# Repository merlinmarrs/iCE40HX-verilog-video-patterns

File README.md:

# Video FPGA Dev Board

A Lattice iCE40HX1K-based FPGA developement board for live-playable video experiments.

|                          |                          |
:-------------------------:|:-------------------------:
  | 

# Features :

- 9-key mechanical button interface
- Relatively low-cost, single board design
- HDMI and VGA out
- Reverse polarity and fuse protection

# Minimal BOM :

[Excel BOM Mouser / Digikey ](https://github.com/merlinmarrs/iCE40HX-verilog-video-patterns/tree/main/PCB%20files)

- 9x Mechanical keyboard keys
- 1x FPGA iCE40HX1K-TQ144
- 1x 100MHz clock oscillator
- 1x SRAM 2Mb 256Kx8
- 1x Flash N25Q032A13ESC40F
- 1x USB-C SMD 6 pin connector
- 1x 3.3V reg TLV73333PDBVT 
- 1x 1.2V reg TLV73312PDBVT
- 1x PFET
- 1x Resettable Fuse
- 1x D-SUB 15 connector
- 1x HDMI Connector 
- 50x 0.1µF capacitor 0805
- 50x  10kΩ, 1.8kΩ, 1kΩ, 470Ω, 270Ω, 120Ω resistors 0805
- 5x LEDs 0805
- 2x Dual-row headers

optional extras : (1x Raspberry Pi Zero, 1x Micro SD holder, 2x 10kΩ potentiometers, 1x fast op-amp, 1x 3.5mm audio jack, 1x dual SMD dip switch, 1x SMD pushbutton)

# PCB files

[KiCAD and Eagle PCBs](https://github.com/merlinmarrs/iCE40HX-verilog-video-patterns/tree/main/PCB%20files)

# HDL files

[Verilog, Pin constraints, and synthesized binaries ](https://github.com/merlinmarrs/iCE40HX-verilog-video-patterns/tree/main/verilog)

To compile and upload files :

[Yoysis Open-source Toolchain ](https://github.com/YosysHQ/yosys)

[iCEcube2 Toolchain](https://www.latticesemi.com/iCEcube2)

## Acknowledgements

Mike Field <hamster@snap.net.nz> for his minimalDVID_encoder.vhd : A quick and dirty DVI-D implementation

OLIMEX FPGA dev board https://github.com/OLIMEX/iCE40HX1K-EVB/tree/master

ALHAMBRA FPGA https://github.com/FPGAwars/Alhambra-II-FPGA/tree/master

HDL Bits https://hdlbits.01xz.net/wiki/Main_Page

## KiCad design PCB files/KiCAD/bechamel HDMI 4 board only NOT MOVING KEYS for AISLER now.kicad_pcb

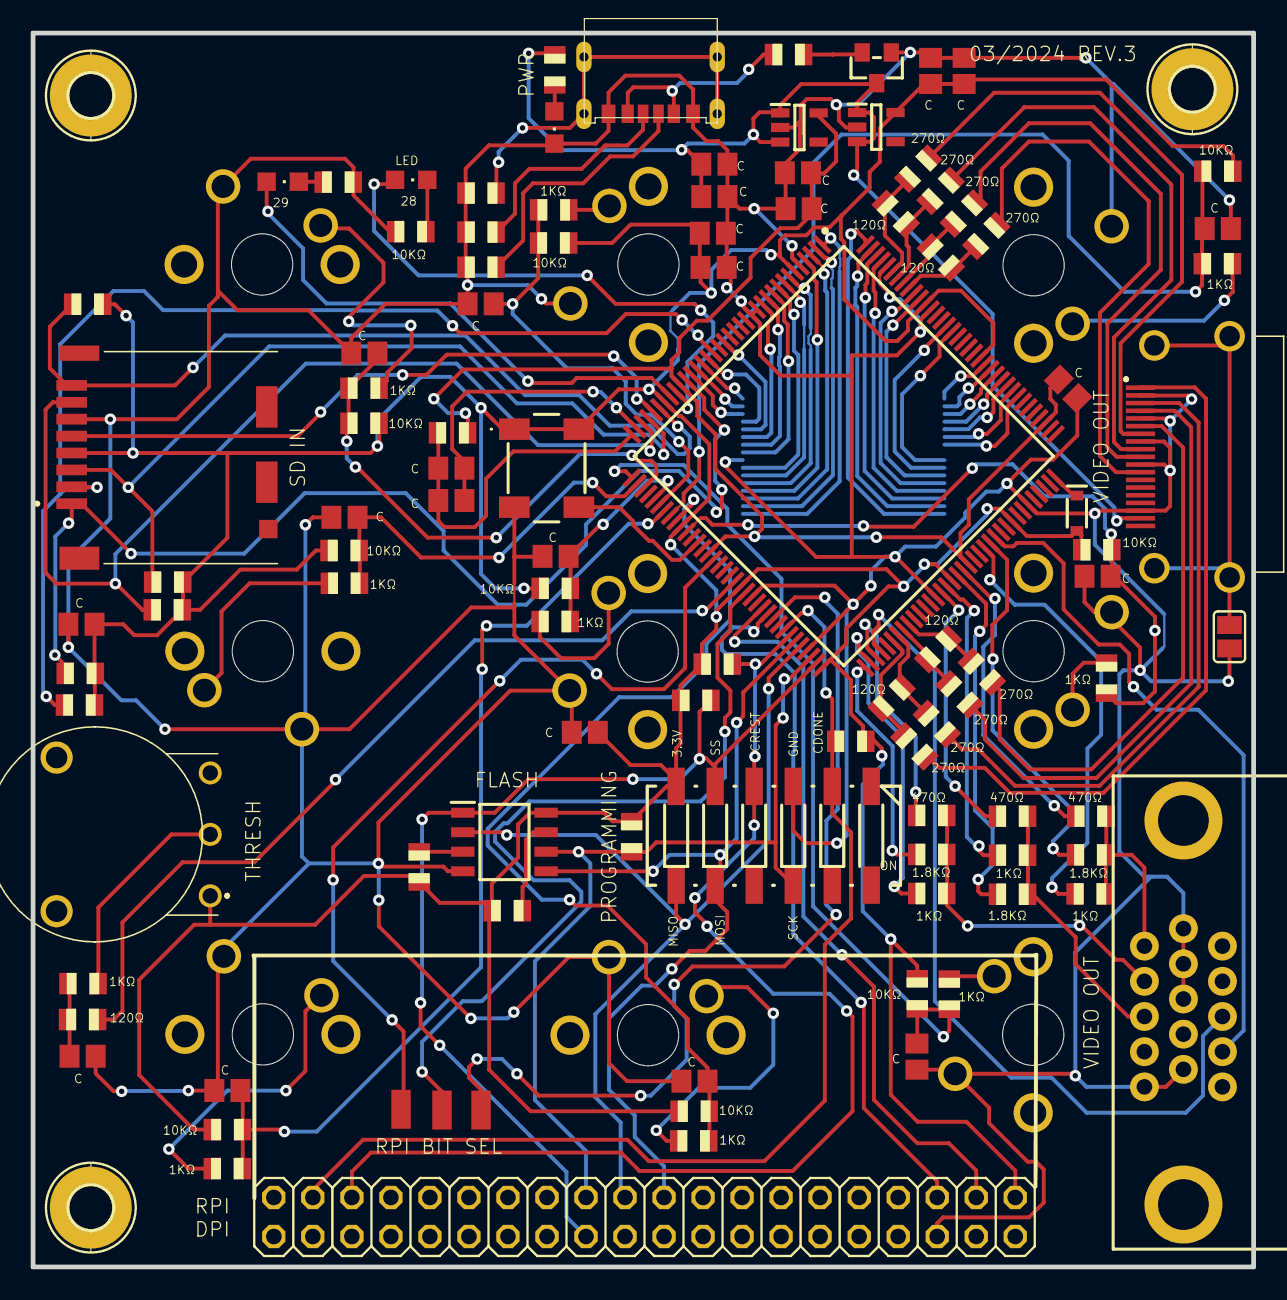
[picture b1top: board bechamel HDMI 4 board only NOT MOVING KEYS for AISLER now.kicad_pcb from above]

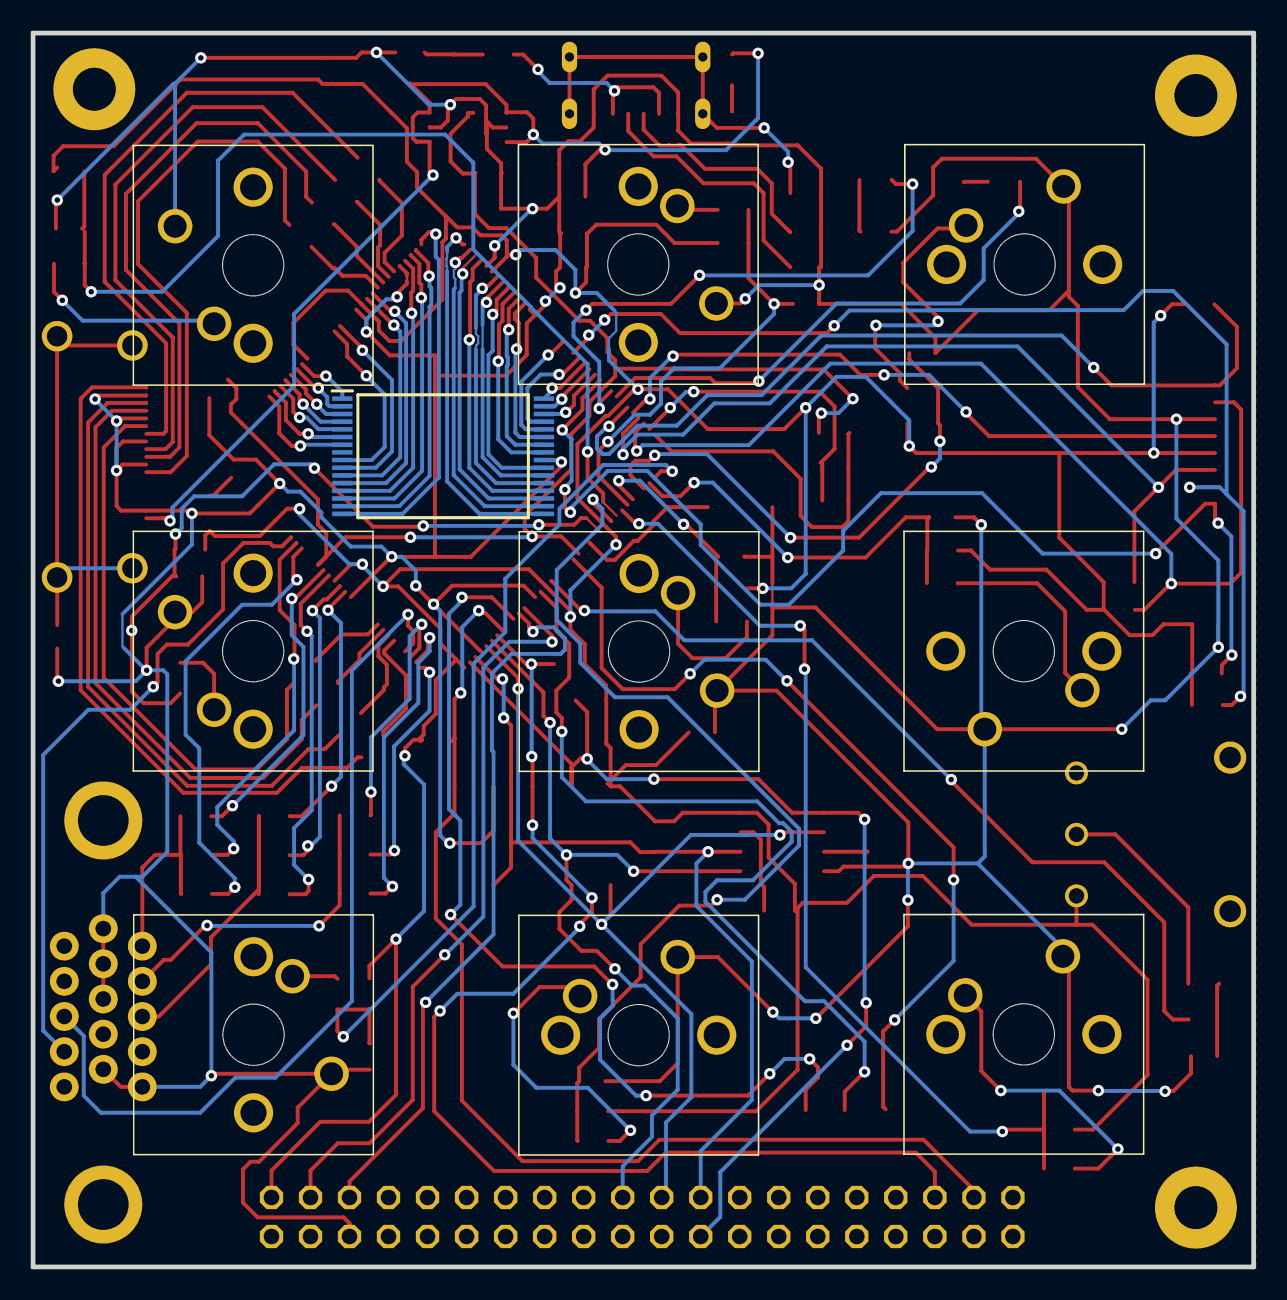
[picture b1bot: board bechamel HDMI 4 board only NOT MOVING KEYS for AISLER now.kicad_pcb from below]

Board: 2 copper layers, 79.5 x 80.3 mm, 117 parts (10 on the bottom side), 119 nets.

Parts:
C1, C6, C7, C8, C9, C10, C11, C12, C13, C14, C15, C18, C21, C22, C25, C26, C27: 0.1uF; C0805
C3, C4, C5, C16, C23: 10uF; C0805
C17: 5.6nF; C0805
D1: 250mA/100V; SOD-323
FUSE0: FUSE; R0805
H1, H5, H6: MOUNT-PAD-ROUND2.8; 2,8-PAD
IC1: TLV73333PDBVT; SOT95P280X145-5N
IC2: ICE40HX1K-TQ144; QFP50P2200X2200X160-144N
IC3: TLV73312PDBVT; SOT95P280X145-5N
IC4: N25Q032A13ESC40F; SOIC127P600X175-8N
IC6: IS62WV2568BLL-55HLI; SOP50P1340X125-32N
J2: SS-53000-001; SS53000001
J3: DM3CS-SF; DM3CSSF
JP1: 2X20
LED6, LED12, LED13: CHIPLED_0805
P-FET2: SOT23-WIDE
PAD1, PAD2, PAD3: SMD1,27-2,54
R1, R17, R25: 470R; R0805
R2, R5, R7, R15, R18, R22, R24, R26, R47, R49, R51, R53: 1K; R0805
R3, R4, R6, R8, R9, R10, R11, R12, R13, R21, R23, R45, R46, R48, R50, R52, R54, R55, R58, R59: 10K; R0805
R14, R36, R37: 100 ohm; R0805
R16, R20, R27: 1.8K; R0805
R19: 300 ohm; R0805
R28, R29, R31, R32, R34, R35, R39, R40: 270R; R0805
R30, R33, R38, R41: 120R; R0805
R42: 1M; R0805
R43, R44: 5k1; R0805
R56: 1K8 ohm; R0805
R57: 180 ohm; R0805
S1, S2, S3, S4, S5, S6, S7, S8, S13: MX1A-11NW; MX1A11NW
S9: 219-06J; CTS-219-06J
SJ2: SJ
U$1: DB15
U$2: USBC-6P; USCX-06FX-XXMX-01
VR1: RV100F-30-4K1B-B10K-B301; RV100F304K1BB10KB301
Y2: ECS-3953M-080-BN-T-TR; ECS3953M080BNTTR

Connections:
1.2V: C4.1, C26.1, C27.1, IC2.27, IC2.51, IC2.92, IC2.111, IC3.5, R14.2
3.3V: C12.1, C15.1, C16.2, C18.1, C21.1, C25.1, D1.A, IC1.5, IC2.6, IC2.30, IC2.46, IC2.57, IC2.72, IC2.89, IC2.100, IC2.123, IC2.133, IC4.8, J3.4, JP1.1, R3.2, R4.2, R6.2, R8.2, R9.2, R10.2, R11.2, R12.2, R13.2, R21.2, R23.2, R45.2, R46.2, R48.2, R50.2, R52.2, R54.2, R55.1, R58.2, R59.2, S9.6, VR1.1, Y2.1, Y2.4
5V: C3.1, C5.1, IC1.1, IC1.3, IC3.1, IC3.3, J2.18, P-FET2.3, R19.2
5V?: FUSE0.1, P-FET2.2
A0: IC2.4, IC6.20
A1: IC2.3, IC6.19
A2: IC2.2, IC6.18
A3: IC2.1, IC6.17
A4: IC2.144, IC6.16
A5: IC2.143, IC6.15
A6: IC2.142, IC6.14
A7: IC2.141, IC6.13
A8: IC2.120, IC6.3
A9: IC2.121, IC6.2
A10: IC2.24, IC6.31
A11: IC2.122, IC6.1
A12: IC2.135, IC6.12
A13: IC2.119, IC6.4
A14: IC2.134, IC6.11
A15: IC2.116, IC6.7
A16: IC2.129, IC6.10
A17: IC2.128, IC6.9
ADC_IN: IC2.56, R57.2
BLUE: R1.2, R15.2, R16.2, U$1.3
BLUE_1: IC2.87, R1.1
BLUE_2: IC2.88, R15.1
BLUE_3: IC2.90, R16.1
CLK+: IC2.137, R39.2, R41.1
CLK-: IC2.136, R40.2, R41.2
CMD: IC2.33, J3.3, R54.1
CS2: IC2.117, IC6.6
DAT0: IC2.34, J3.7, R55.2
DAT1: IC2.31, J3.8, R59.1
DAT2: IC2.26, J3.1, R45.1
DAT3: IC2.21, J3.2, R58.1
DATA0+: IC2.139, R34.2, R38.1
DATA0-: IC2.138, R35.2, R38.2
DATA1+: IC2.80, R31.2, R33.1
DATA1-: IC2.81, R32.2, R33.2
DATA2+: IC2.78, R28.2, R30.1
DATA2-: IC2.79, R29.2, R30.2
FPGA_CLK: IC2.49, Y2.3
GND: C1.1, C3.2, C4.2, C5.2, C6.1, C7.1, C8.1, C9.1, C10.1, C11.1, C12.2, C13.1, C14.1, C15.2, C16.1, C17.1, C18.2, C21.2, C25.2, C26.2, C27.2, IC1.2, IC2.5, IC2.13, IC2.14, IC2.59, IC2.69, IC2.86, IC2.103, IC2.132, IC2.140, IC3.2, IC4.4, IC6.24, J2.2, J2.5, J2.8, J2.11, J2.17, J3.6, JP1.6, LED6.C, P-FET2.1, R36.1, R37.1, R42.2, R43.2, R44.2, S1.2, S2.2, S3.2, S4.2, S5.2, S6.2, S7.2, S8.2, S9.3, S13.2, SJ2.2, U$1.5, U$1.6, U$1.7, U$1.8, U$1.10, U$2.GND1, U$2.GND2, Y2.2
GREEN: R17.2, R18.2, R20.2, U$1.2
GREEN_1: IC2.75, R17.1
GREEN_2: IC2.74, R18.1
GREEN_3: IC2.73, R20.1
H_SYNC: IC2.76, U$1.13
H_SYNC_IN: IC2.62, JP1.5
I/O0: IC2.7, IC6.21
I/O1: IC2.8, IC6.22
I/O2: IC2.9, IC6.23
I/O3: IC2.10, IC6.25
I/O4: IC2.11, IC6.26
I/O5: IC2.12, IC6.27
I/O6: IC2.19, IC6.28
I/O7: IC2.22, IC6.29
ICE_CDONE: IC2.65, JP1.37, R8.1, S9.2
ICE_CREST: IC2.66, JP1.35, R9.1, S9.4
ICE_MISO: IC2.68, IC4.2, JP1.21, S9.7
ICE_MOSI: IC2.67, IC4.5, JP1.19, S9.8
ICE_SCK: IC2.70, IC4.6, JP1.23, R13.1, S9.10
ICE_SS_B: IC2.71, IC4.1, JP1.24, R12.1, S9.5
KEY_0: C13.2, IC2.37, R50.1, R51.2
KEY_0_LED: IC2.28, LED12.A
KEY_1: C6.2, IC2.38, R3.1, R5.2
KEY_1_LED: IC2.29, LED13.A
KEY_2: C11.2, IC2.39, R48.1, R49.2
KEY_3: C1.2, IC2.41, R2.2, R4.1
KEY_4: C10.2, IC2.42, R46.1, R47.2
KEY_5: C7.2, IC2.43, R6.1, R7.2
KEY_6: C9.2, IC2.44, R23.1, R24.2
KEY_7: C8.2, IC2.45, R21.1, R22.2
KEY_8: C14.2, IC2.47, R52.1, R53.2
unnamed: IC4.7, R10.1
unnamed: LED6.A, R19.1
unnamed: IC4.3, R11.1
unnamed: R43.1, U$2.CC2
unnamed: D1.C, IC2.108
unnamed: C22.2, C23.2, IC2.35
unnamed: C22.1, C23.1, IC2.36, R14.1
unnamed: R42.1, U$2.SHIELD1, U$2.SHIELD2, U$2.SHIELD3, U$2.SHIELD4
unnamed: R56.2, VR1.2
unnamed: J2.1, R28.1
unnamed: R44.1, U$2.CC1
unnamed: J2.MH1, J2.MH2, J2.MH3, J2.MH4, SJ2.1
unnamed: C17.2, R56.1, R57.1
unnamed: J2.3, R29.1
unnamed: J2.4, R31.1
unnamed: LED12.C, R36.2
unnamed: LED13.C, R37.2
unnamed: J2.6, R32.1
unnamed: IC2.52, PAD1.1
unnamed: J2.7, R34.1
unnamed: J2.9, R35.1
unnamed: J2.10, R39.1
unnamed: J2.12, R40.1
unnamed: R2.1, S6.1
unnamed: R5.1, S5.1
unnamed: R7.1, S7.1
unnamed: R22.1, S8.1
unnamed: R24.1, S3.1
unnamed: R47.1, S2.1
unnamed: R49.1, S1.1
unnamed: R51.1, S13.1
unnamed: R53.1, S4.1
unnamed: IC2.58, PAD2.1
unnamed: IC2.63, PAD3.1
PRE_FUSE: FUSE0.2, U$2.VBUS1, U$2.VBUS2
RED: R25.2, R26.2, R27.2, U$1.1
RED_1: IC2.91, R25.1
RED_2: IC2.95, R26.1
RED_3: IC2.96, R27.1
SD_CLK: IC2.32, J3.5
V_SYNC: IC2.97, U$1.14
V_SYNC_IN: IC2.61, JP1.3
~CS1: IC2.25, IC6.30
~OE: IC2.23, IC6.32
~WE: IC2.118, IC6.5

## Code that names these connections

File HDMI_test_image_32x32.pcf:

set_io hdmi_p[0] 139 -io_std SB_LVCMOS
set_io hdmi_p[2] 78 -io_std SB_LVCMOS
set_io hdmi_p[1] 80 -io_std SB_LVCMOS
set_io hdmi_p[3] 137 -io_std SB_LVCMOS

set_io hdmi_n[0] 138 -io_std SB_LVCMOS
set_io hdmi_n[2] 79 -io_std SB_LVCMOS
set_io hdmi_n[1] 81 -io_std SB_LVCMOS
set_io hdmi_n[3] 136 -io_std SB_LVCMOS

set_io key[0] 37
set_io key[1] 38
set_io key[2] 39
set_io key[3] 41
set_io key[4] 42
set_io key[5] 43
set_io key[6] 44
set_io key[7] 45
set_io rec 47

set_io SCK 32
set_io CMD 33

set_io LED1 29
set_io LED5 28

set_io reset 66

set_io clk100 49

set_io b_in 62

set_io v_sync 97 //for vga
set_io h_sync 76 //for vga

set_io io[0] 7
set_io io[1] 8
set_io io[2] 9
set_io io[3] 10
set_io io[4] 11
set_io io[5] 12
set_io io[6] 19
set_io io[7] 22

set_io addr[0] 4
set_io addr[1] 3
set_io addr[2] 2
set_io addr[3] 1
set_io addr[4] 144
set_io addr[5] 143
set_io addr[6] 142
set_io addr[7] 141
set_io addr[8] 120
set_io addr[9] 121
set_io addr[10] 24
set_io addr[11] 122
set_io addr[12] 135
set_io addr[13] 119
set_io addr[14] 134
set_io addr[15] 116
set_io addr[16] 129
set_io addr[17] 128


set_io cs 25
set_io oe 23
set_io we 118

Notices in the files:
README.md:
License: MIT
